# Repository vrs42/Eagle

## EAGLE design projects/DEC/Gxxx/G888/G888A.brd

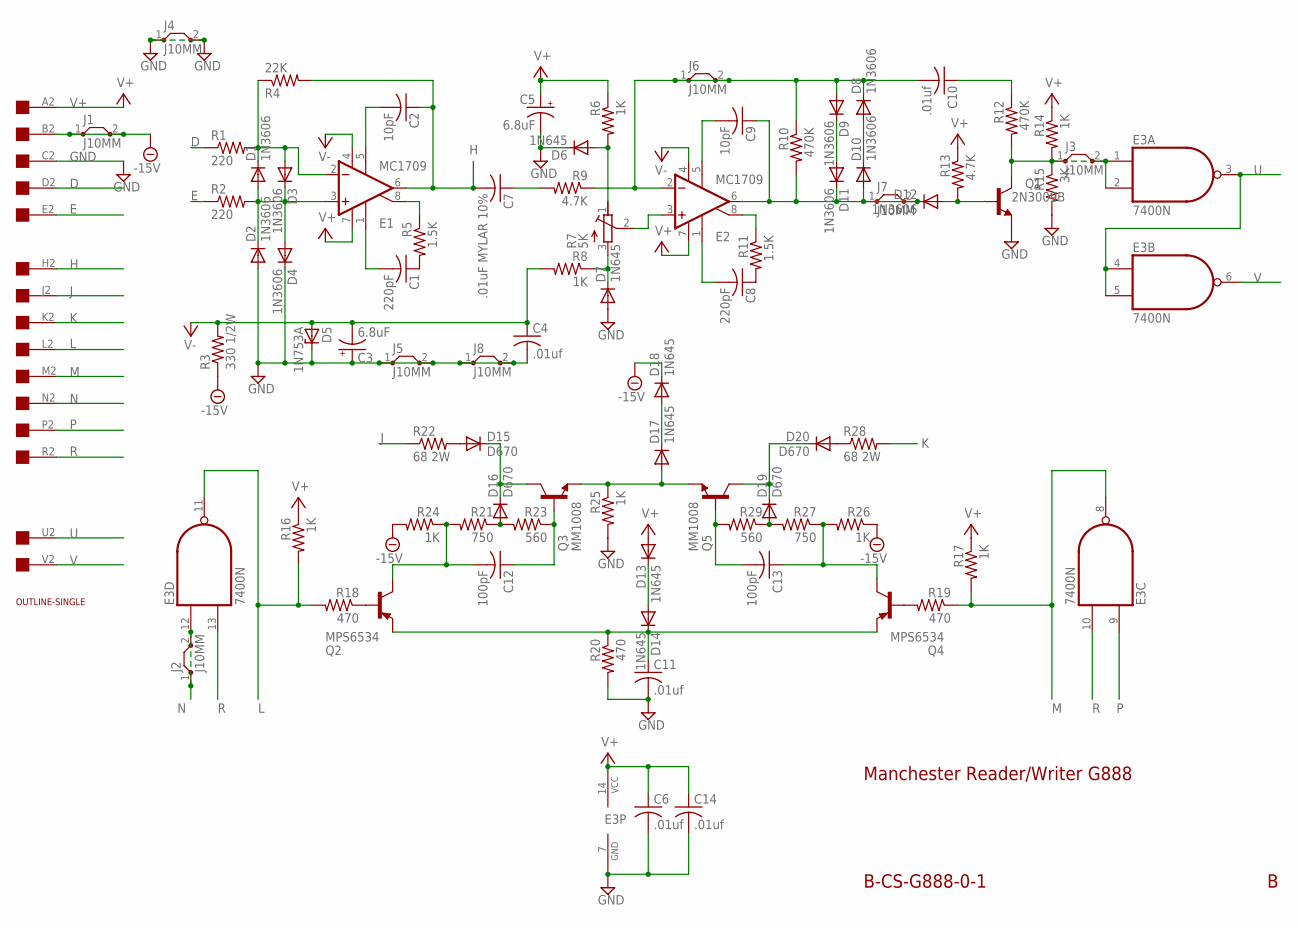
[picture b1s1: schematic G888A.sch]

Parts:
C1, C8: 220pF; C050-025X075
C2, C9: 10pF; C050-025X075
C3, C5: 6.8uF; E12-8
C4, C6, C10, C11, C14: .01uf; C050-025X075
C7: .01uF MYLAR 10%; C225-062X268
C12, C13: 100pF; C050-025X075
D1, D2, D3, D4, D8, D9, D10, D11, D12: 1N3606; DO35-10
D5: 1N753A; DO35Z10
D6, D7, D13, D14, D17, D18: 1N645; DO35-10
D15, D16, D19, D20: D670; DO35-10
E1, E2: MC1709; H08C
E3: 7400N; DIL14
J1, J2, J3, J4, J5, J6, J7, J8: J10MM; 10
Q1: 2N3009B; TO39
Q2, Q4: MPS6534; TO39
Q3, Q5: MM1008; TO39
R1, R2: 220; 0207/10
R3: 330 1/2W; 0411/15
R4: 22K; 0207/10
R5, R11: 1.5K; 0207/10
R6, R8, R14, R16, R17, R24, R25, R26: 1K; 0207/10
R7: 5K; 3006Y
R9, R13: 4.7K; 0207/10
R10, R12: 470K; 0207/10
R15: 3K; 0207/10
R18, R19, R20: 470; 0207/10
R21, R27: 750; 0207/10
R22, R28: 68 2W; P0817/22
R23, R29: 560; 0207/10
U$1: EDGE-1; EDGE-CON1
U$4: OUTLINE-SINGLE; SINGLE

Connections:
-15V: D18.C, J1.1, J1.2, R3.1, R24.2, R26.1, U$1.B2
D: R1.1, U$1.D2
E: R2.1, U$1.E2
GND: C3.+, C4.2, C5.-, C6.2, C11.2, C14.2, D2.A, D4.C, D5.C, D6.C, D7.A, E3.7 (GND), J4.1, J4.2, J5.1, J5.2, J8.1, J8.2, Q1.1 (E), R15.2, R20.2, R25.2, U$1.C2
H: C2.1, C7.2, E1.6 (OUT), R4.2, U$1.H2
J: R22.1, U$1.J2
K: R28.2, U$1.K2
L: E3.11 (O), R16.2, R18.2, U$1.L2
M: E3.8 (O), R17.2, R19.1, U$1.M2
N: E3.12 (I0), J2.1, J2.2, U$1.N2
unnamed: C1.1, R5.2
unnamed: C8.1, R11.2
unnamed: D1.C, D3.A, E1.2 (-IN), R1.2, R4.1
unnamed: D1.A, D2.C, D3.C, D4.A, E1.3 (+IN), R2.2
unnamed: C8.2, E2.1 (ON1)
unnamed: C1.2, E1.1 (ON1)
unnamed: E1.8 (ON2), R5.1
unnamed: C2.2, E1.5 (OPT)
unnamed: D6.A, R6.2, R7.1 (A)
unnamed: C10.2, D8.C, D9.A, E2.2 (-IN), J6.1, J6.2, R9.1, R10.1
unnamed: E2.3 (+IN), R7.2 (S)
unnamed: D7.C, R7.3 (E), R8.1
unnamed: E2.8 (ON2), R11.1
unnamed: C9.2, E2.5 (OPT)
unnamed: C9.1, D10.A, D11.C, D12.C, E2.6 (OUT), J7.1, J7.2, R10.2
unnamed: C7.1, R9.2
unnamed: D9.C, D11.A
unnamed: D8.A, D10.C
unnamed: C10.1, R12.1
unnamed: D12.A, Q1.2 (B), R13.2
unnamed: E3.1 (I0), E3.2 (I1), J3.1, J3.2, Q1.3 (C), R12.2, R14.2, R15.1
unnamed: D17.A, Q3.1 (E), Q5.1 (E), R25.1
unnamed: C11.1, D14.C, Q2.1 (E), Q4.1 (E), R20.1
unnamed: D13.C, D14.A
unnamed: Q2.2 (B), R18.1
unnamed: Q4.2 (B), R19.2
unnamed: D15.A, R22.2
unnamed: D16.A, R21.1, R23.2
unnamed: C12.2, Q2.3 (C), R21.2, R24.1
unnamed: C12.1, Q3.2 (B), R23.1
unnamed: D19.A, R27.2, R29.1
unnamed: C13.1, Q4.3 (C), R26.2, R27.1
unnamed: C13.2, Q5.2 (B), R29.2
unnamed: D20.A, R28.1
unnamed: D15.C, D16.C, Q3.3 (C)
unnamed: D19.C, D20.C, Q5.3 (C)
unnamed: D17.C, D18.A
P: E3.9 (I0), U$1.P2
R: E3.10 (I1), E3.13 (I1), U$1.R2
U: E3.3 (O), E3.4 (I0), E3.5 (I1), U$1.U2
V: E3.6 (O), U$1.V2
V+: C5.+, C6.1, C14.1, D13.A, E1.7 (V+), E2.7 (V+), E3.14 (VCC), R6.1, R13.1, R14.1, R16.1, R17.1, U$1.A2
V-: C3.-, C4.1, D5.A, E1.4 (V-), E2.4 (V-), R3.2, R8.2

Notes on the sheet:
Manchester Reader/Writer G888
B-CS-G888-0-1

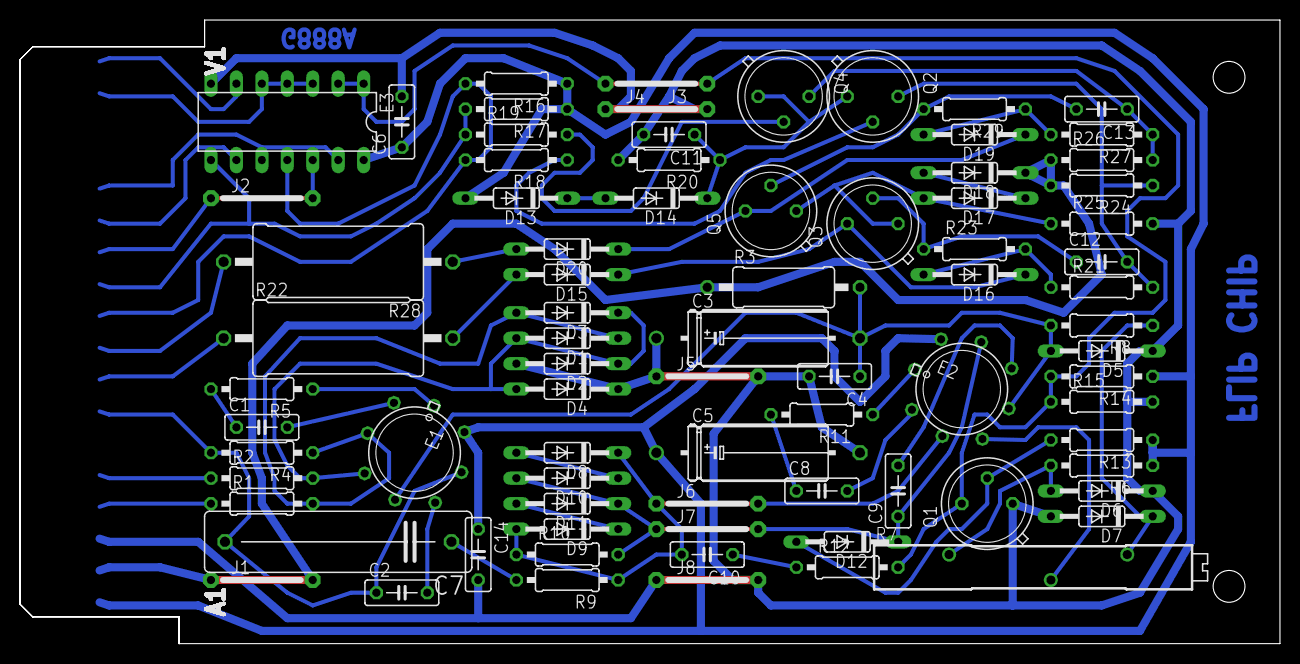
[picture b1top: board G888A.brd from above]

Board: 2 copper layers, 125.7 x 62.2 mm, 81 parts (0 on the bottom side), 53 nets.

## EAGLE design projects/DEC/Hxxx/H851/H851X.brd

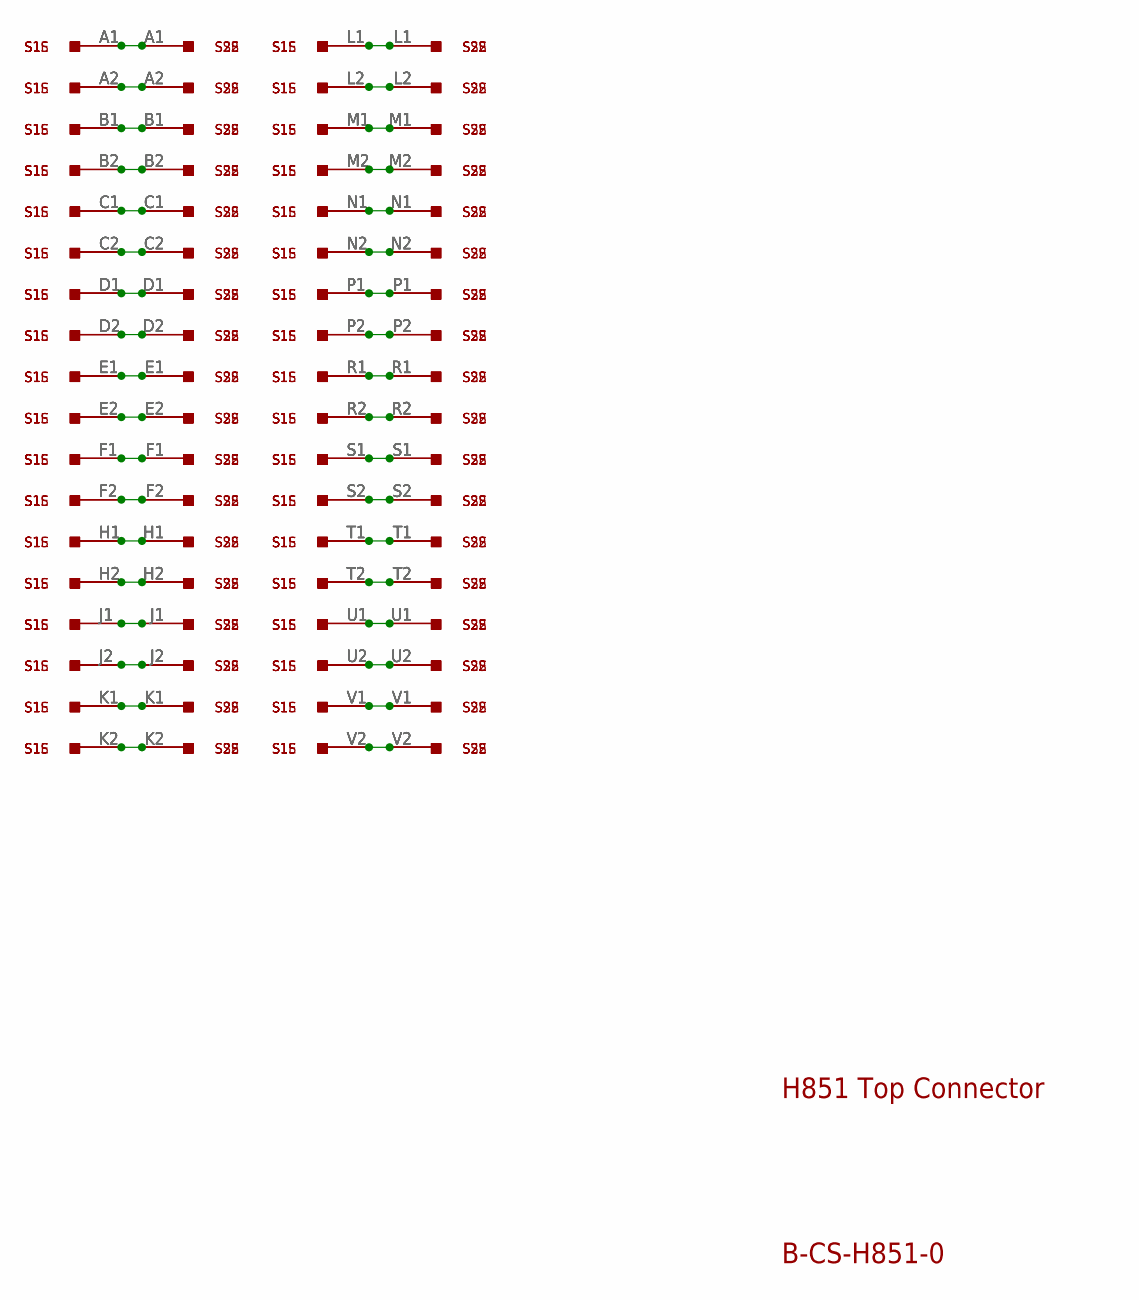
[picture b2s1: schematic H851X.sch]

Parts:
S1, S2: M916; H807
S1E, S2E: M916EDAC; EDAC346-36
S1S, S2S: M916ECS; ECS2418

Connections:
unnamed: S1.L1, S1E.L1, S1S.L1, S2.L1, S2E.L1, S2S.L1
unnamed: S1.L2, S1E.L2, S1S.L2, S2.L2, S2E.L2, S2S.L2
unnamed: S1.M1, S1E.M1, S1S.M1, S2.M1, S2E.M1, S2S.M1
unnamed: S1.M2, S1E.M2, S1S.M2, S2.M2, S2E.M2, S2S.M2
unnamed: S1.N1, S1E.N1, S1S.N1, S2.N1, S2E.N1, S2S.N1
unnamed: S1.N2, S1E.N2, S1S.N2, S2.N2, S2E.N2, S2S.N2
unnamed: S1.P1, S1E.P1, S1S.P1, S2.P1, S2E.P1, S2S.P1
unnamed: S1.P2, S1E.P2, S1S.P2, S2.P2, S2E.P2, S2S.P2
unnamed: S1.R1, S1E.R1, S1S.R1, S2.R1, S2E.R1, S2S.R1
unnamed: S1.R2, S1E.R2, S1S.R2, S2.R2, S2E.R2, S2S.R2
unnamed: S1.S1, S1E.S1, S1S.S1, S2.S1, S2E.S1, S2S.S1
unnamed: S1.S2, S1E.S2, S1S.S2, S2.S2, S2E.S2, S2S.S2
unnamed: S1.T1, S1E.T1, S1S.T1, S2.T1, S2E.T1, S2S.T1
unnamed: S1.T2, S1E.T2, S1S.T2, S2.T2, S2E.T2, S2S.T2
unnamed: S1.U1, S1E.U1, S1S.U1, S2.U1, S2E.U1, S2S.U1
unnamed: S1.U2, S1E.U2, S1S.U2, S2.U2, S2E.U2, S2S.U2
unnamed: S1.V1, S1E.V1, S1S.V1, S2.V1, S2E.V1, S2S.V1
unnamed: S1.V2, S1E.V2, S1S.V2, S2.V2, S2E.V2, S2S.V2
unnamed: S1.A1, S1E.A1, S1S.A1, S2.A1, S2E.A1, S2S.A1
unnamed: S1.A2, S1E.A2, S1S.A2, S2.A2, S2E.A2, S2S.A2
unnamed: S1.B1, S1E.B1, S1S.B1, S2.B1, S2E.B1, S2S.B1
unnamed: S1.B2, S1E.B2, S1S.B2, S2.B2, S2E.B2, S2S.B2
unnamed: S1.C1, S1E.C1, S1S.C1, S2.C1, S2E.C1, S2S.C1
unnamed: S1.C2, S1E.C2, S1S.C2, S2.C2, S2E.C2, S2S.C2
unnamed: S1.D1, S1E.D1, S1S.D1, S2.D1, S2E.D1, S2S.D1
unnamed: S1.D2, S1E.D2, S1S.D2, S2.D2, S2E.D2, S2S.D2
unnamed: S1.E1, S1E.E1, S1S.E1, S2.E1, S2E.E1, S2S.E1
unnamed: S1.E2, S1E.E2, S1S.E2, S2.E2, S2E.E2, S2S.E2
unnamed: S1.F1, S1E.F1, S1S.F1, S2.F1, S2E.F1, S2S.F1
unnamed: S1.F2, S1E.F2, S1S.F2, S2.F2, S2E.F2, S2S.F2
unnamed: S1.H1, S1E.H1, S1S.H1, S2.H1, S2E.H1, S2S.H1
unnamed: S1.H2, S1E.H2, S1S.H2, S2.H2, S2E.H2, S2S.H2
unnamed: S1.J1, S1E.J1, S1S.J1, S2.J1, S2E.J1, S2S.J1
unnamed: S1.J2, S1E.J2, S1S.J2, S2.J2, S2E.J2, S2S.J2
unnamed: S1.K1, S1E.K1, S1S.K1, S2.K1, S2E.K1, S2S.K1
unnamed: S1.K2, S1E.K2, S1S.K2, S2.K2, S2E.K2, S2S.K2

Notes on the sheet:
H851 Top Connector
B-CS-H851-0

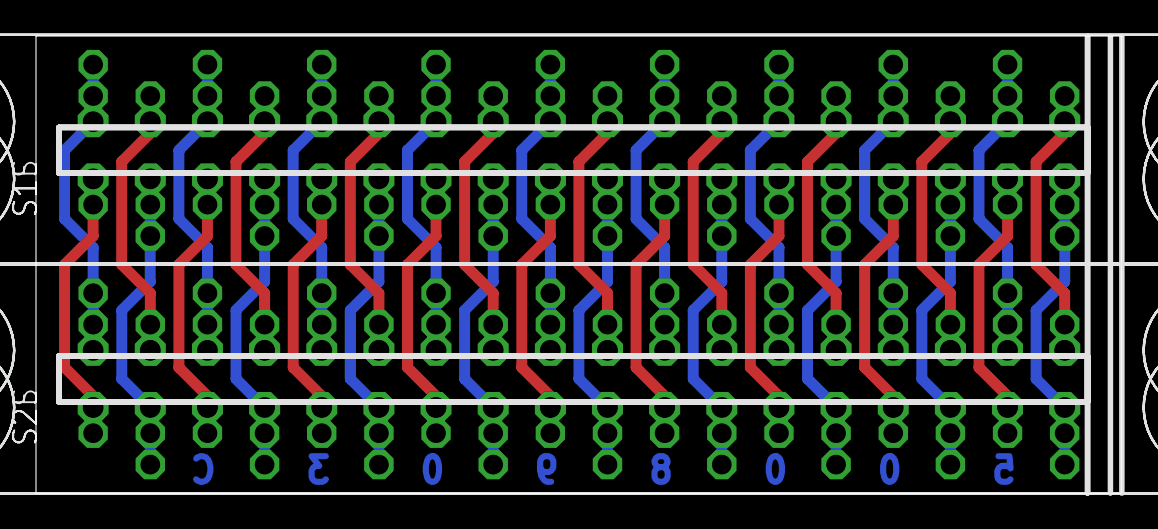
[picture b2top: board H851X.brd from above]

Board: 2 copper layers, 60.3 x 25.4 mm, 6 parts (0 on the bottom side), 36 nets.
